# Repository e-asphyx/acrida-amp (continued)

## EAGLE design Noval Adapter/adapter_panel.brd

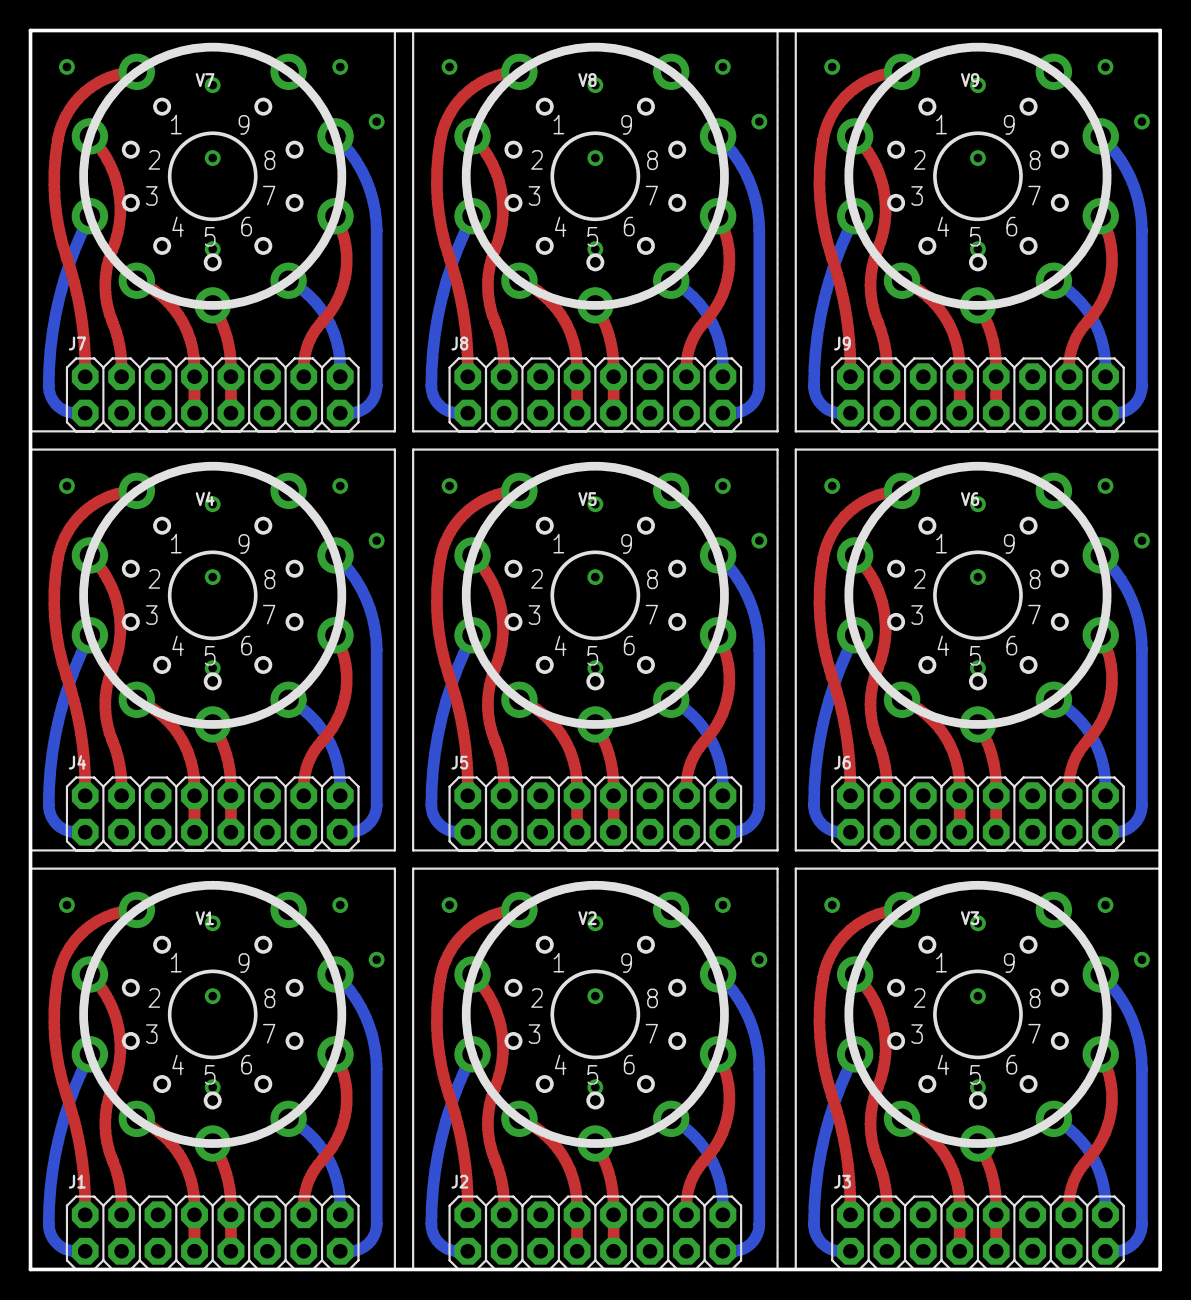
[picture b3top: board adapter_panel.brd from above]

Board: 2 copper layers, 78.7 x 86.4 mm, 18 parts (0 on the bottom side), 81 nets.

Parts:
J1, J2, J3, J4, J5, J6, J7, J8, J9: 2X8
V1, V2, V3, V4, V5, V6, V7, V8, V9: NOVAL-18MM

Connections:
AG: J1.4, V1.2
AG1: J2.4, V2.2
AG2: J3.4, V3.2
AG3: J4.4, V4.2
AG4: J5.4, V5.2
AG5: J6.4, V6.2
AG6: J7.4, V7.2
AG7: J8.4, V8.2
AG8: J9.4, V9.2
AK: J1.1, V1.3
AK1: J2.1, V2.3
AK2: J3.1, V3.3
AK3: J4.1, V4.3
AK4: J5.1, V5.3
AK5: J6.1, V6.3
AK6: J7.1, V7.3
AK7: J8.1, V8.3
AK8: J9.1, V9.3
AP: J1.2, V1.1
AP1: J2.2, V2.1
AP2: J3.2, V3.1
AP3: J4.2, V4.1
AP4: J5.2, V5.1
AP5: J6.2, V6.1
AP6: J7.2, V7.1
AP7: J8.2, V8.1
AP8: J9.2, V9.1
BG: J1.14, V1.7
BG1: J2.14, V2.7
BG2: J3.14, V3.7
BG3: J4.14, V4.7
BG4: J5.14, V5.7
BG5: J6.14, V6.7
BG6: J7.14, V7.7
BG7: J8.14, V8.7
BG8: J9.14, V9.7
BK: J1.15, V1.8
BK1: J2.15, V2.8
BK2: J3.15, V3.8
BK3: J4.15, V4.8
BK4: J5.15, V5.8
BK5: J6.15, V6.8
BK6: J7.15, V7.8
BK7: J8.15, V8.8
BK8: J9.15, V9.8
BP: J1.16, V1.6
BP1: J2.16, V2.6
BP2: J3.16, V3.6
BP3: J4.16, V4.6
BP4: J5.16, V5.6
BP5: J6.16, V6.6
BP6: J7.16, V7.6
BP7: J8.16, V8.6
BP8: J9.16, V9.6
GND: J1.3, J1.5, J1.6, J1.11, J1.12, J1.13
GND1: J2.3, J2.5, J2.6, J2.11, J2.12, J2.13
GND2: J3.3, J3.5, J3.6, J3.11, J3.12, J3.13
GND3: J4.3, J4.5, J4.6, J4.11, J4.12, J4.13
GND4: J5.3, J5.5, J5.6, J5.11, J5.12, J5.13
GND5: J6.3, J6.5, J6.6, J6.11, J6.12, J6.13
GND6: J7.3, J7.5, J7.6, J7.11, J7.12, J7.13
GND7: J8.3, J8.5, J8.6, J8.11, J8.12, J8.13
GND8: J9.3, J9.5, J9.6, J9.11, J9.12, J9.13
H1: J1.9, J1.10, V1.5
H2: J1.7, J1.8, V1.4
H3: J2.9, J2.10, V2.5
H4: J2.7, J2.8, V2.4
H5: J3.9, J3.10, V3.5
H6: J3.7, J3.8, V3.4
H7: J4.9, J4.10, V4.5
H8: J4.7, J4.8, V4.4
H9: J5.9, J5.10, V5.5
H10: J5.7, J5.8, V5.4
H11: J6.9, J6.10, V6.5
H12: J6.7, J6.8, V6.4
H13: J7.9, J7.10, V7.5
H14: J7.7, J7.8, V7.4
H15: J8.9, J8.10, V8.5
H16: J8.7, J8.8, V8.4
H17: J9.9, J9.10, V9.5
H18: J9.7, J9.8, V9.4

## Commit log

2017-02-12 Initial
2017-02-12 Back to gain stage with uncompensated PSN
2017-02-14 PDFs
2017-02-14 More meqasures
2017-02-15 Horizontal version
2017-02-15 Minor tweaks
2017-02-15 A bit more room for tube cooling
2017-02-15 Move LED to canter
2017-02-15 Snap in cap
2017-02-15 No silk for vregs
2017-02-20 Split groundplane again
2017-02-20 Oops
2017-03-04 Values fixed
2017-03-18 Adapter board
2017-03-29 Improved auto biasing circuit
2017-03-29 Back to toroidal transformer
2017-06-01 New board again
2017-06-02 Small changes
2017-06-03 Ground plane on top
2017-06-03 Optional protection circuit
2017-06-05 Final polishing
2017-07-27 Capacitors polarity was reversed
2017-08-01 Adjust some components a bit
2017-08-01 Use snap in caps
2017-08-01 Small adjustments
2017-08-02 TO-220 redrawn for perfect fit into grid
